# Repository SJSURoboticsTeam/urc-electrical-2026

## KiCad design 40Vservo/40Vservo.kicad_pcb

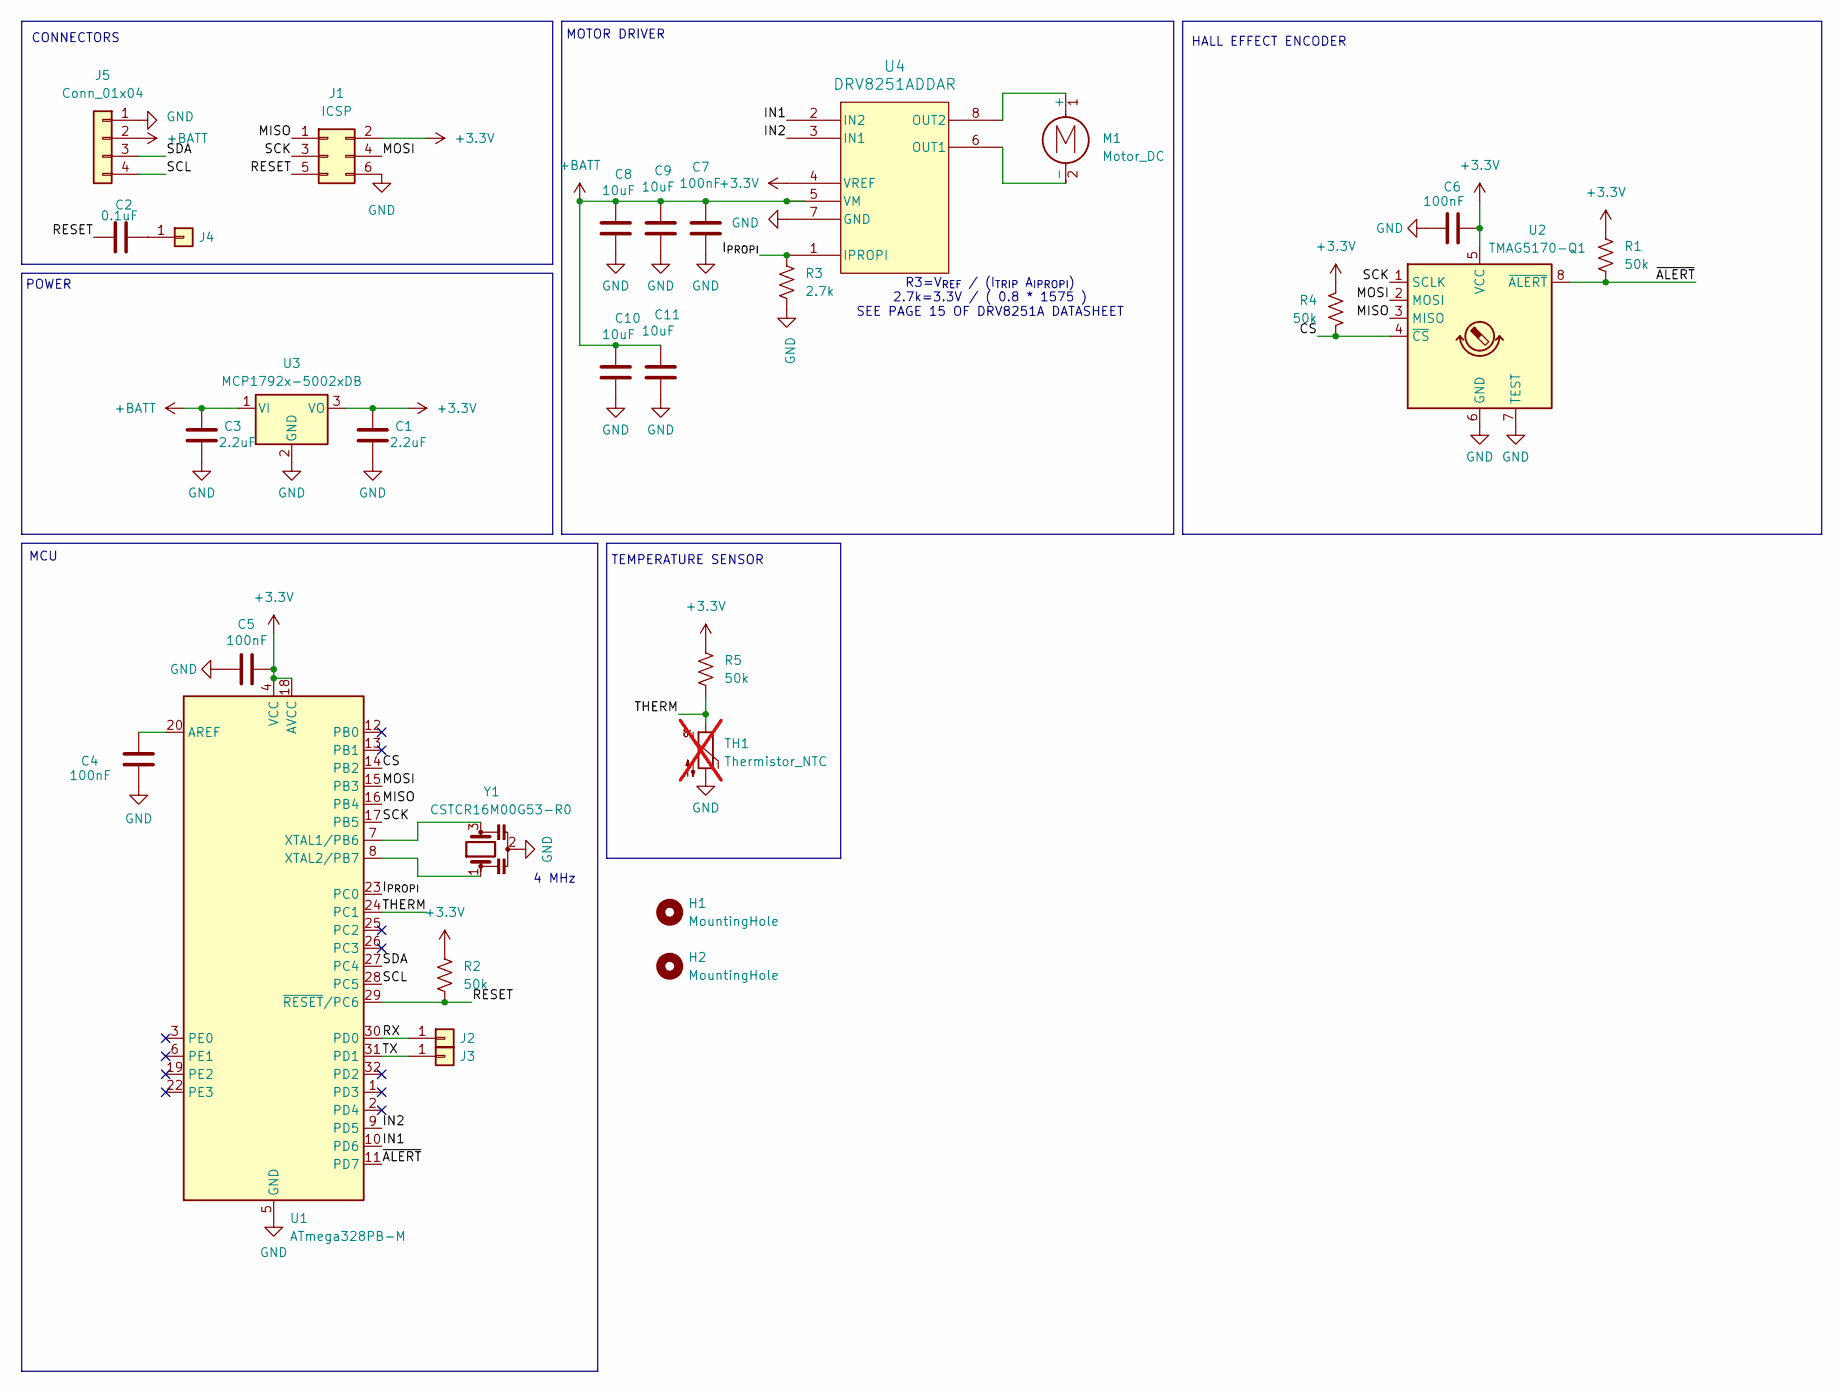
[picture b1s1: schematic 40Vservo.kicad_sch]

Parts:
C1, C3: 2.2uF; C_0603_1608Metric_Pad1.08x0.95mm_HandSolder; LCSC Part # C23630
C2: 0.1uF; C_0603_1608Metric_Pad1.08x0.95mm_HandSolder; LCSC Part # C14663
C4, C5, C6: 100nF; C_0603_1608Metric_Pad1.08x0.95mm_HandSolder; LCSC Part # C23630
C7: 100nF; C_0603_1608Metric_Pad1.08x0.95mm_HandSolder; LCSC Part # C14663
C8, C9, C10, C11: 10uF; C_0805_2012Metric_Pad1.18x1.45mm_HandSolder; LCSC Part # C440198
H1, H2: MountingHole; MountingHole_2.2mm_M2
J1: ICSP; POGO_ISP
J2, J3, J4: Conn_01x01; SolderWirePad_1x01_SMD_1x2mm
J5: Conn_01x04; SolderWire-0.5sqmm_1x04_P4.6mm_D0.9mm_OD2.1mm
M1: Motor_DC; PinHeader_1x02_P2.54mm_Vertical
R1, R2, R4, R5: 50k; R_0603_1608Metric_Pad0.98x0.95mm_HandSolder; LCSC Part # C23206
R3: 2.7k; R_0603_1608Metric_Pad0.98x0.95mm_HandSolder; LCSC Part # C13167
TH1: Thermistor_NTC; R_0603_1608Metric_Pad0.98x0.95mm_HandSolder; not fitted
U1: ATmega328PB-M; QFN-32-1EP_5x5mm_P0.5mm_EP3.1x3.1mm; LCSC Part # C967933
U2: TMAG5170-Q1; VSSOP-8_3.0x3.0mm_P0.65mm
U3: MCP1792x-5002xDB; SOT-223-3_TabPin2
U4: DRV8251ADDAR; Texas_HSOP-8-1EP_3.9x4.9mm_P1.27mm; LCSC Part # C5218844
Y1: CSTCR16M00G53-R0; Resonator_SMD_Murata_CSTxExxV-3Pin_3.0x1.1mm_HandSoldering

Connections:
+3.3V: C1.1, C5.2, C6.2, J1.2, R1.1, R2.1, R4.2, R5.1, U1.4 (VCC), U1.18 (AVCC), U2.5 (VCC), U3.3 (VO), U4.4 (VREF)
+BATT: C2.2, C3.1, C7.1, C8.1, C9.1, C10.1, C11.1, J4.1, J5.2, U3.1 (VI), U4.5 (VM)
/CS: R4.1, U1.14 (PB2), U2.4 (~CS)
/IN1: U1.10 (PD6), U4.2 (IN2)
/IN2: U1.9 (PD5), U4.3 (IN1)
/I_{PROPI}: R3.1, U1.23 (PC0), U4.1 (IPROPI)
/MISO: J1.1, U1.16 (PB4), U2.3 (MISO)
/MOSI: J1.4, U1.15 (PB3), U2.2 (MOSI)
/RX: J2.1, U1.30 (PD0)
/SCK: J1.3, U1.17 (PB5), U2.1 (SCLK)
/SCL: J5.4, U1.28 (PC5)
/SDA: J5.3, U1.27 (PC4)
/THERM: R5.2, TH1.1, U1.24 (PC1)
/TX: J3.1, U1.31 (PD1)
/~ALERT: R1.2, U1.11 (PD7), U2.8 (~ALERT)
unnamed: M1.1 (+), U4.8 (OUT2)
unnamed: M1.2 (-), U4.6 (OUT1)
unnamed: C4.2, U1.20 (AREF)
unnamed: U1.7 (XTAL1/PB6), Y1.3
unnamed: U1.8 (XTAL2/PB7), Y1.1

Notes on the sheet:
4 MHz
HALL EFFECT ENCODER
MCU
MOTOR DRIVER
TEMPERATURE SENSOR
R3=V_{REF} / (I_{TRIP} A_{IPROPI}) 2.7k=3.3V / ( 0.8 * 1575 ) SEE PAGE 15 OF DRV8251A DATASHEET
POWER
CONNECTORS

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
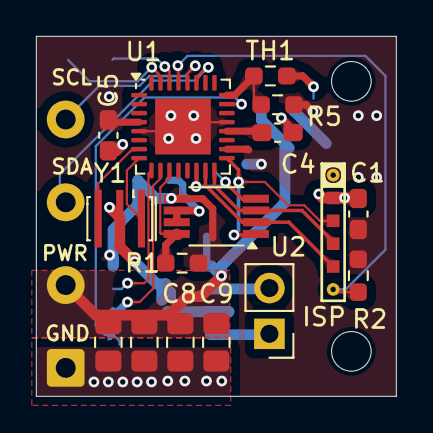
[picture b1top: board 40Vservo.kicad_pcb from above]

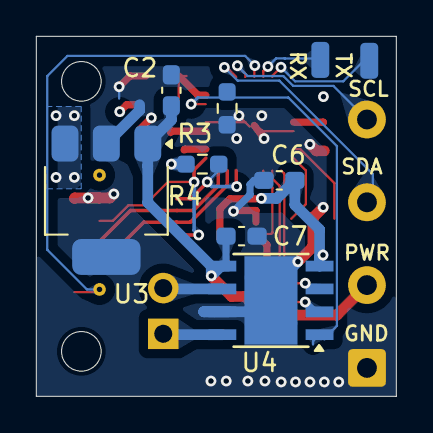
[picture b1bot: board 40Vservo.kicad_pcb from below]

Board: 4 copper layers, 20.0 x 20.0 mm, 28 parts (10 on the bottom side), 22 nets.

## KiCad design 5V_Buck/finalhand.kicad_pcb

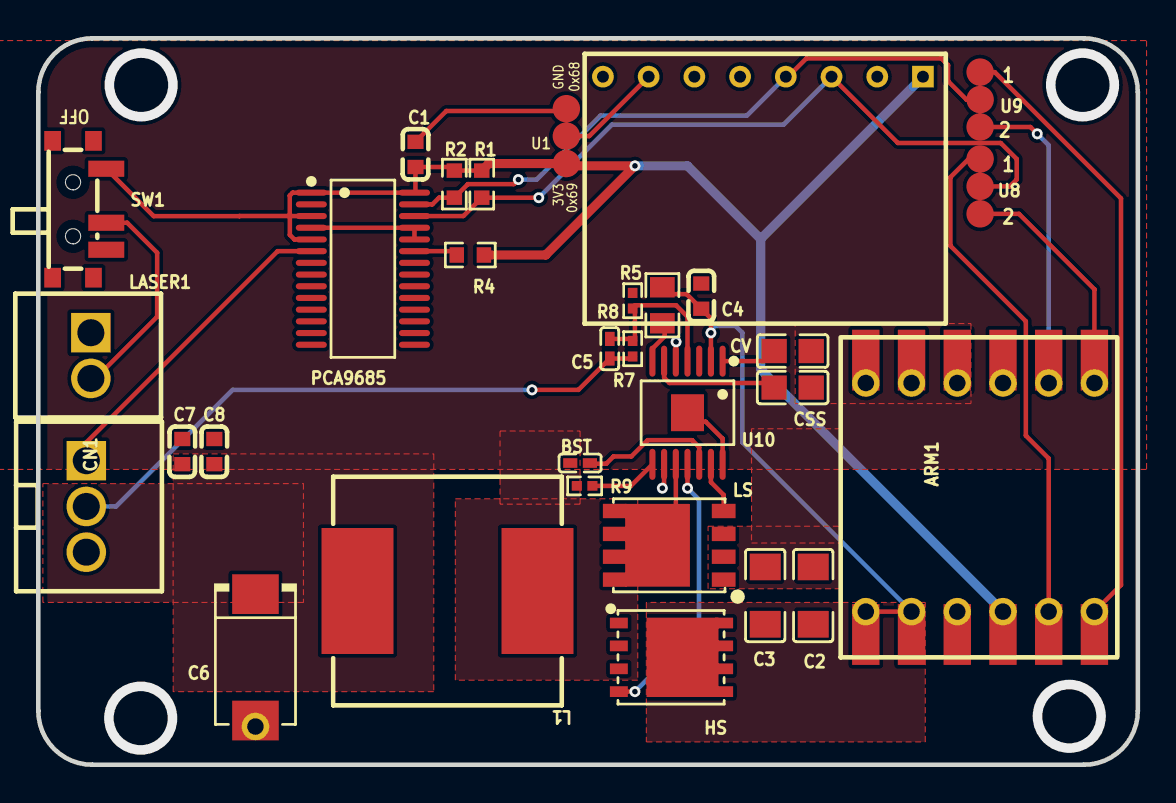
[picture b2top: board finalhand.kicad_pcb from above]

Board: 4 copper layers, 61.1 x 40.4 mm, 31 parts (0 on the bottom side), 23 nets.

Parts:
ARM1: USB-C Stubby
BST: C0402
C1, C4, C7, C8: C0603
C2, C3: C1206
C5: C0402
C6: CAP-SMD_L7.3-W4.3-R-RD
CN1: CONN-TH_3P-P2.54_KF2EDGV-2.54-3P
CSS: C0805
CV: C0805
HS: DFN-8_L5.9-W5.2-P1.27-LS6.2-BL
L1: IND-SMD_L12.7-W12.7
LASER1: CONN-TH_KF2EDGV-2.54-2P
LS: POWERVDFN-8_L6.0-W5.0-P1.27-BL
PCA9685: TSSOP-28_L9.7-W4.4-P0.65-LS6.4-BL
R1, R2, R4: R0603
R5: R0805
R7, R8, R9: R0402
SW1: SW-SMD_MK-12C02-G020
U1: MPU6050 AD0 Breakout
U6: MPU-6050 MODULE
U8, U9: 3 Pad Jumper
U10: HTSSOP-14_L5.0-W4.4-P0.65-LS6.4-BL-EP

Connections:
3V3: ARM1.4, C1.2, PCA9685.1, PCA9685.3, PCA9685.5, PCA9685.28, R1.2, R2.2, R4.2, SW1.1, U1.3, U6.1
5V: C5.1, C6.1, C7.1, C8.1, CN1.2, L1.2, R7.2
$1N15372: LASER1.2, SW1.2
$1N15383: PCA9685.23, R4.1
$2N671: BST.1, U10.12
$2N681: R5.1, U10.7
$2N1026: CSS.2, U10.6
$2N1121: CV.2, U10.1
$2N1983: C5.2, R7.1, R8.2, U10.4
$2N2778: BST.2, HS.1, HS.2, HS.3, L1.1, LS.5, LS.6, LS.7, LS.8, LS.9, R9.2, U10.10
$2N2800: LS.4, U10.13
$2N2931: R9.1, U10.8
AD0: U1.2, U6.7
GATE: HS.4, U10.11
GND: ARM1.10, ARM1.11, ARM1.12, C1.1, C2.1, C3.1, C4.1, C6.2, C7.2, C8.2, CN1.3, CSS.1, CV.1, LASER1.1, LS.1, LS.2, LS.3, PCA9685.2, PCA9685.4, PCA9685.14, PCA9685.24, PCA9685.25, R8.1, SW1.6, SW1.7, U1.1, U6.2, U10.5, U10.9, U10.14, U10.15
I2C_SCL: ARM1.7, U8.1
I2C_SCL1: ARM1.5, U8.3
I2C_SDA: ARM1.8, U9.1
I2C_SDA1: ARM1.6, U9.3
SCL: PCA9685.26, R1.1, U6.3, U8.2
SDA: PCA9685.27, R2.1, U6.4, U9.2
SERVO: CN1.1, PCA9685.6
VARM: ARM1.1, ARM1.2, C2.2, C3.2, C4.2, HS.5, HS.6, HS.7, HS.8, HS.9, R5.2, U10.2

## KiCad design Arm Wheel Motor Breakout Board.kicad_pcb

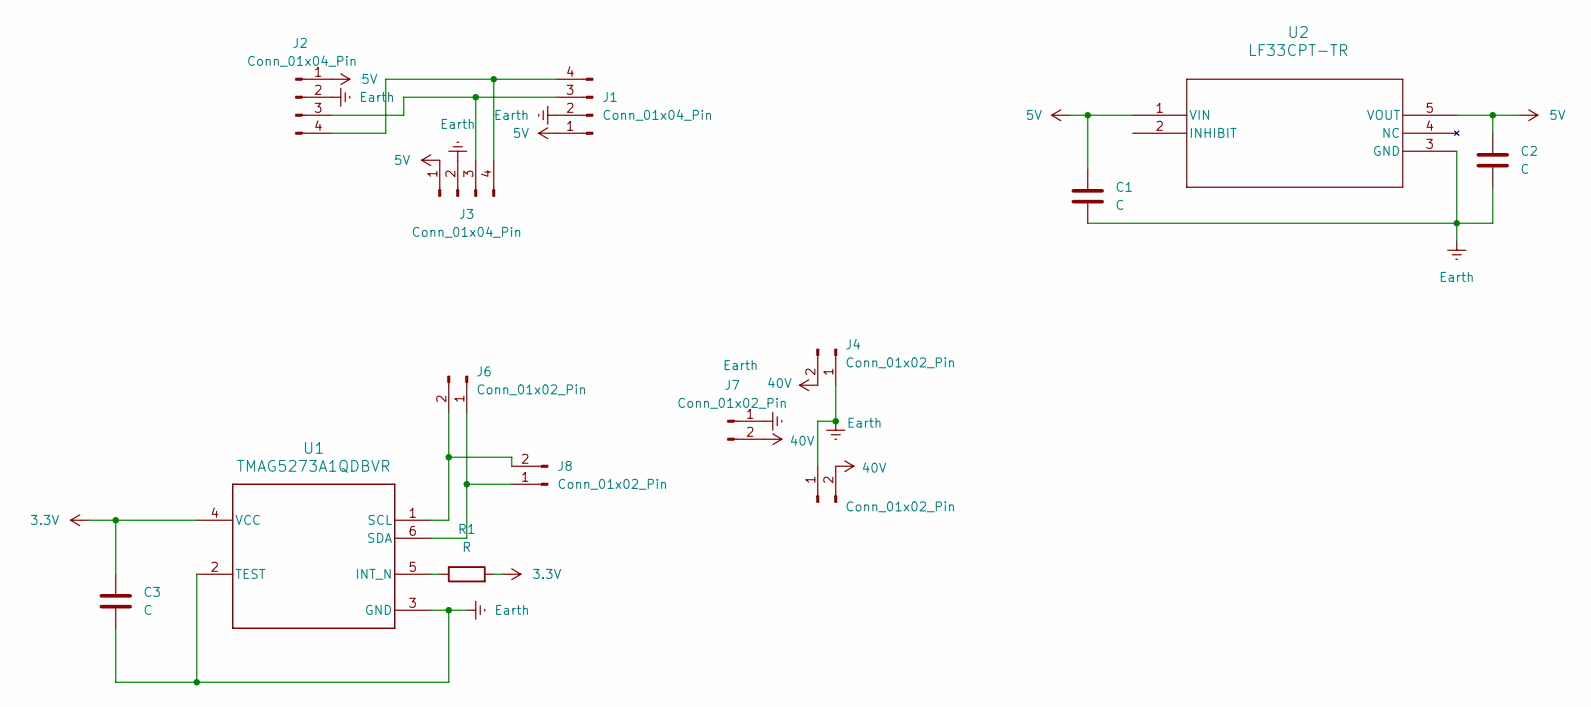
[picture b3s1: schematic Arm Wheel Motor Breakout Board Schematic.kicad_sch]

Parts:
C1, C2, C3: C; C_0201_0603Metric
J1, J2, J3: Conn_01x04_Pin; PhoenixContact_MC_1,5_4-G-3.5_1x04_P3.50mm_Horizontal
J4, J5, J7: Conn_01x02_Pin; AMASS_XT60PW-M_1x02_P7.20mm_Horizontal
J6, J8: Conn_01x02_Pin; PhoenixContact_MC_1,5_2-G-3.5_1x02_P3.50mm_Horizontal
R1: R; R_0201_0603Metric
U1: TMAG5273A1QDBVR; DBV0006A-IPC_A
U2: LF33CPT-TR; PPAK_CPT-TR_STM

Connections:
3.3V: C3.1, R1.2, U1.4 (VCC)
5V: C1.1, C2.1, J1.1, J2.1, J3.1, U2.1 (VIN), U2.5 (VOUT)
40V: J4.2, J5.2, J7.2
Earth: C1.2, C2.2, C3.2, J1.2, J2.2, J3.2, J4.1, J5.1, J7.1, U1.2 (TEST), U1.3 (GND), U2.3 (GND)
unnamed: J1.3, J2.3, J3.3
unnamed: J1.4, J2.4, J3.4
unnamed: J6.1, J8.1, U1.6 (SDA)
unnamed: J6.2, J8.2, U1.1 (SCL)
unnamed: R1.1, U1.5 (INT_N)

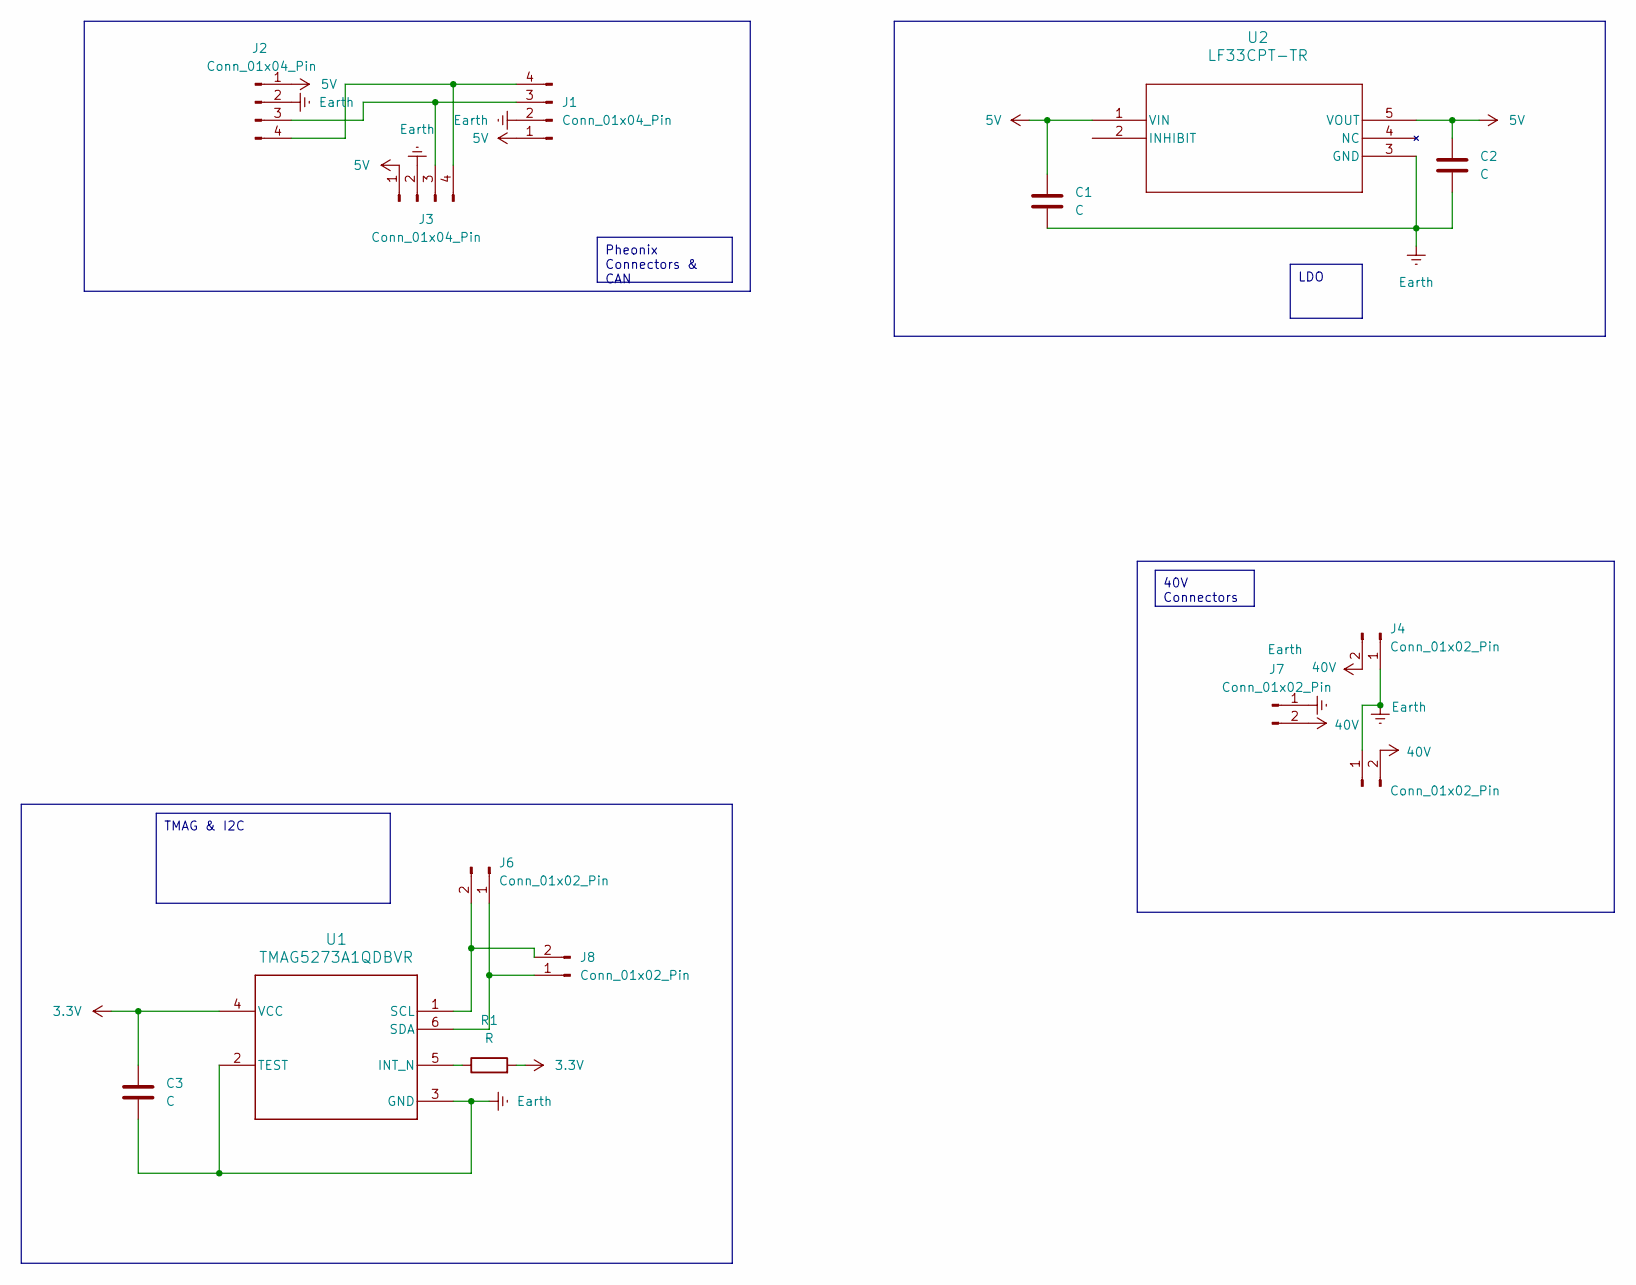
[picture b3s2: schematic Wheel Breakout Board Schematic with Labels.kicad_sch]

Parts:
C1, C2, C3: C; C_0201_0603Metric
J1, J2, J3: Conn_01x04_Pin; PhoenixContact_MC_1,5_4-G-3.5_1x04_P3.50mm_Horizontal
J4, J5, J7: Conn_01x02_Pin; AMASS_XT60PW-M_1x02_P7.20mm_Horizontal
J6, J8: Conn_01x02_Pin; PhoenixContact_MC_1,5_2-G-3.5_1x02_P3.50mm_Horizontal
R1: R; R_0201_0603Metric
U1: TMAG5273A1QDBVR; DBV0006A-IPC_A
U2: LF33CPT-TR; PPAK_CPT-TR_STM

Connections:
3.3V: C3.1, R1.2, U1.4 (VCC)
5V: C1.1, C2.1, J1.1, J2.1, J3.1, U2.1 (VIN), U2.5 (VOUT)
40V: J4.2, J5.2, J7.2
Earth: C1.2, C2.2, C3.2, J1.2, J2.2, J3.2, J4.1, J5.1, J7.1, U1.2 (TEST), U1.3 (GND), U2.3 (GND)
unnamed: J1.3, J2.3, J3.3
unnamed: J1.4, J2.4, J3.4
unnamed: J6.1, J8.1, U1.6 (SDA)
unnamed: J6.2, J8.2, U1.1 (SCL)
unnamed: R1.1, U1.5 (INT_N)

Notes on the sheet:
LDO
TMAG & I2C
Pheonix Connectors & CAN
40V Connectors

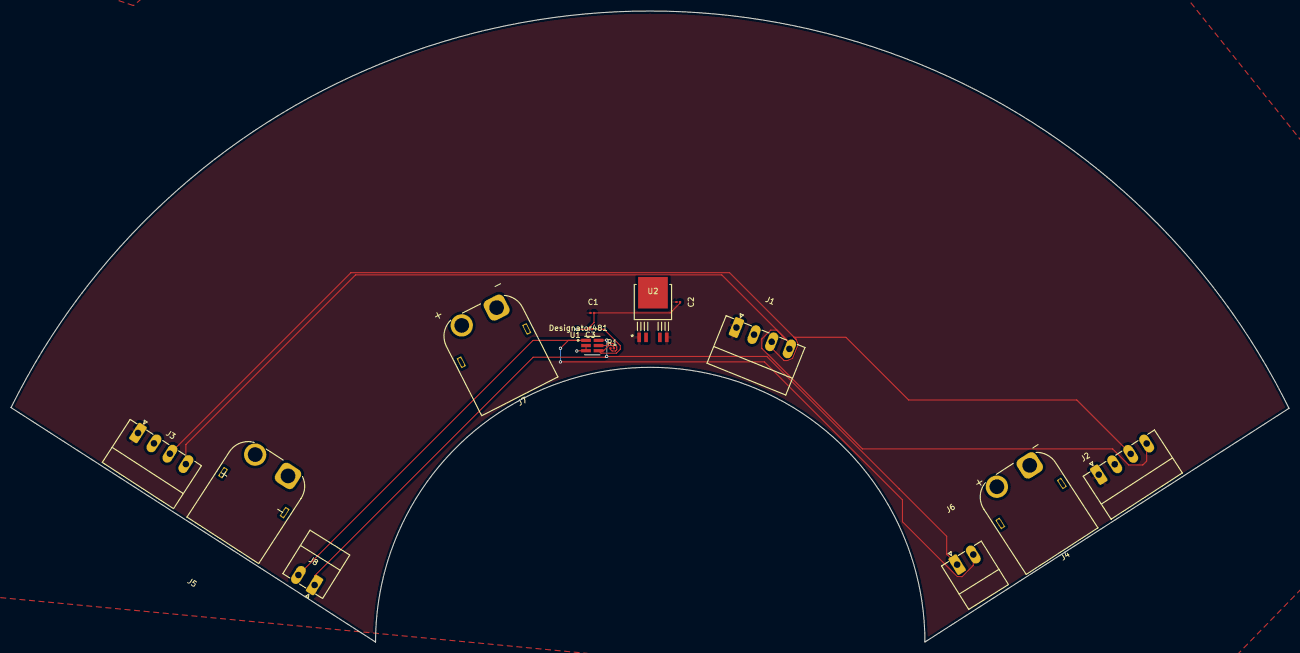
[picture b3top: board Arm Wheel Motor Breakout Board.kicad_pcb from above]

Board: 4 copper layers, 234.9 x 116.0 mm, 14 parts (0 on the bottom side), 9 nets.

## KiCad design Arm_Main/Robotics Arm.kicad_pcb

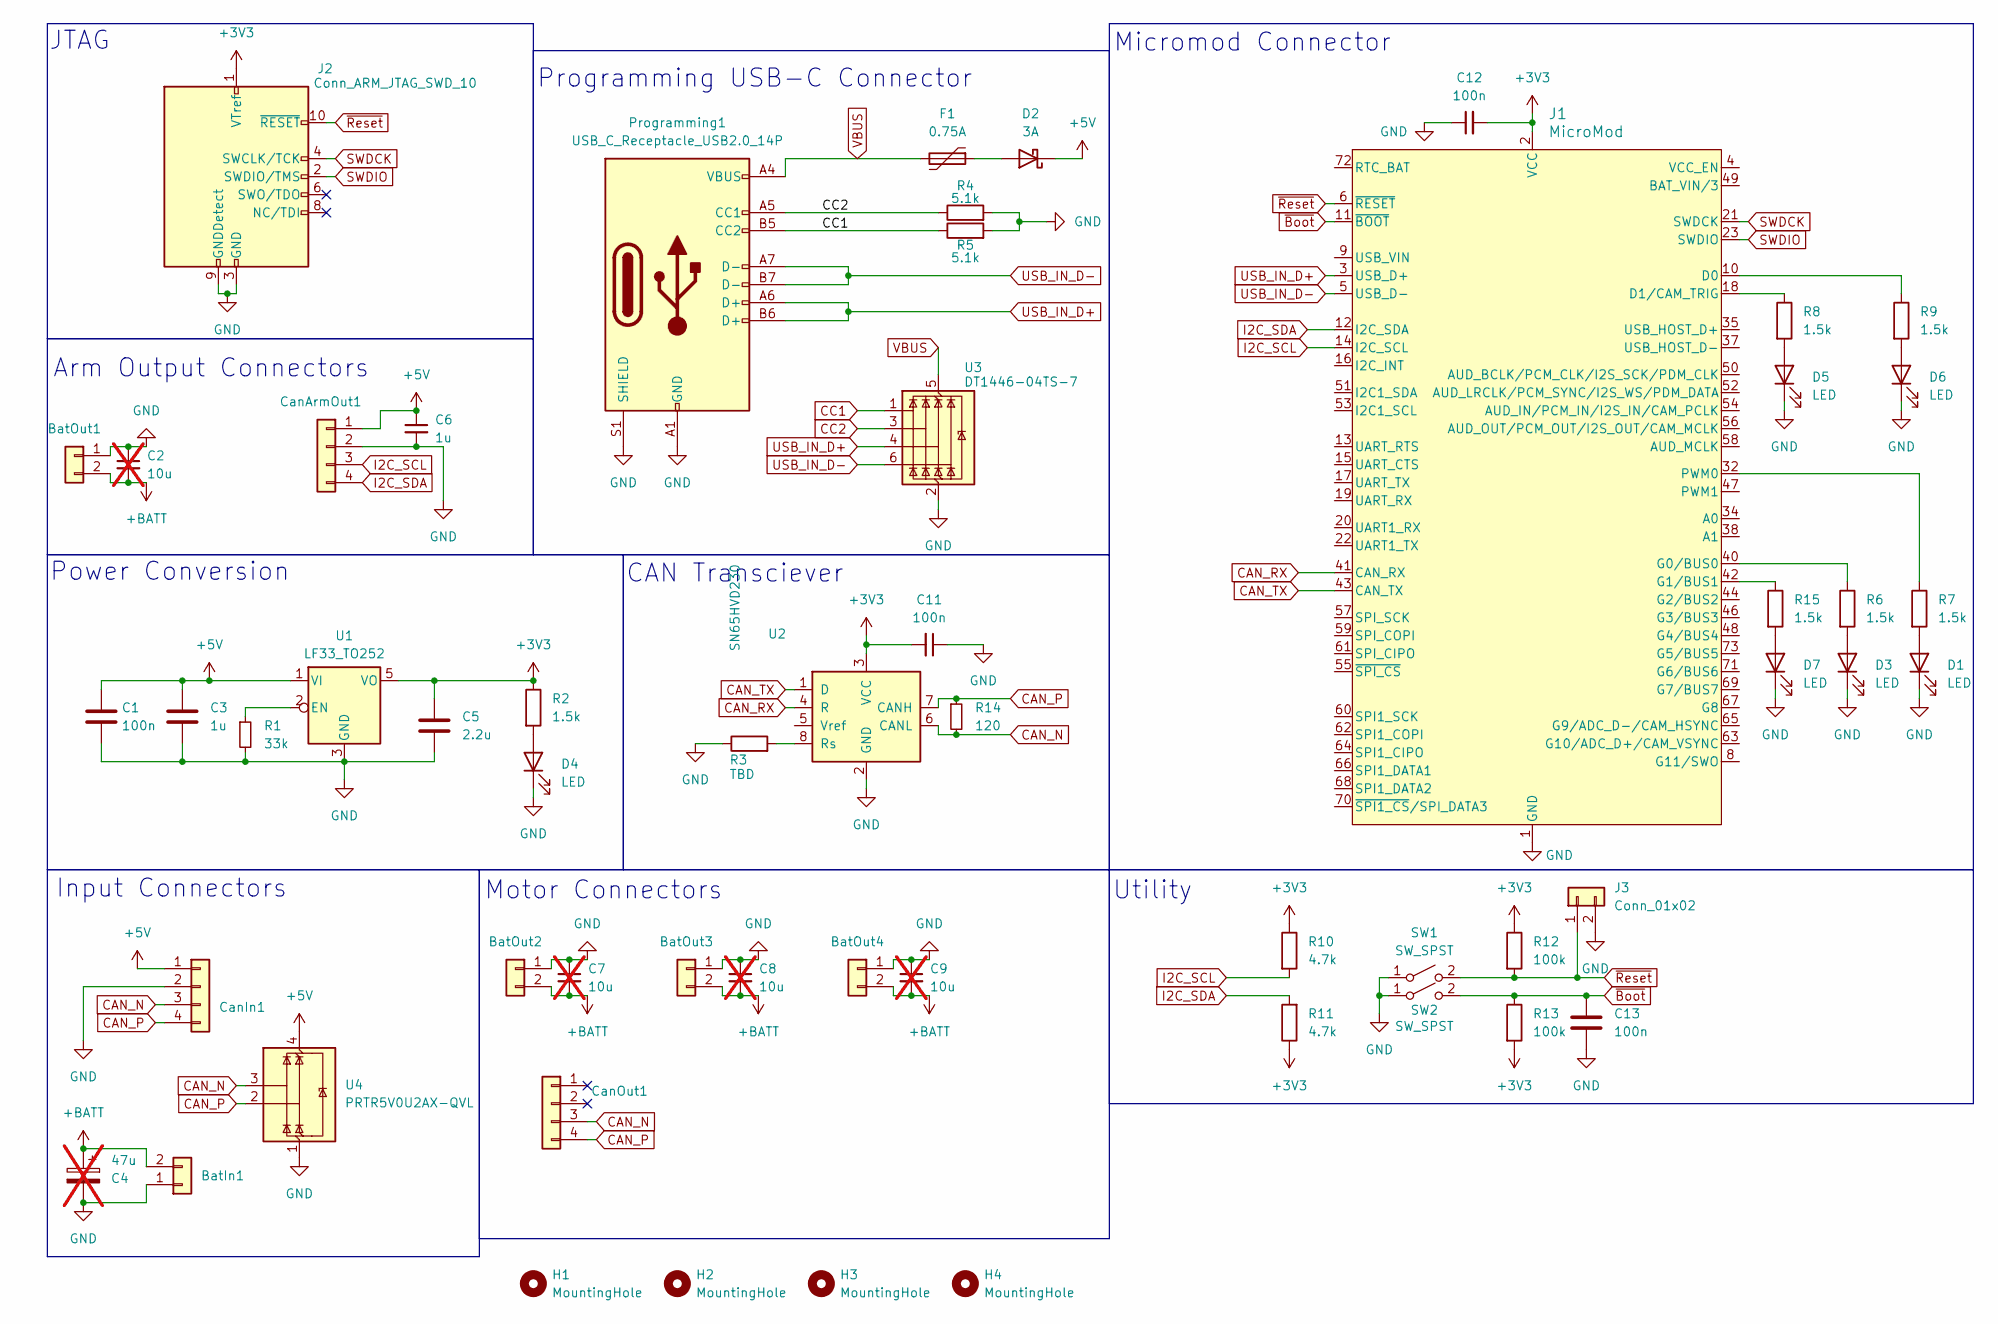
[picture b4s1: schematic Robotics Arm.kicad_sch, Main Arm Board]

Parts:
BatIn1: Conn_01x02_MountingPin; AMASS_XT60PW-F_1x02_P7.20mm_Horizontal
BatOut1, BatOut2, BatOut3, BatOut4: Conn_01x02_MountingPin; AMASS_XT60PW-F_1x02_P7.20mm_Horizontal
C1, C11, C12, C13: 100n; C_0603_1608Metric_Pad1.08x0.95mm_HandSolder
C2, C7, C8, C9: 10u; C_0603_1608Metric_Pad1.08x0.95mm_HandSolder; not fitted
C3, C6: 1u; C_0603_1608Metric_Pad1.08x0.95mm_HandSolder
C4: 47u; CP_Radial_D6.3mm_P2.50mm; not fitted
C5: 2.2u; C_0603_1608Metric_Pad1.08x0.95mm_HandSolder
CanArmOut1: Conn_01x04_MountingPin; Pluggable_Terminal_2.54mm_4P_Horizontal
CanIn1: Conn_01x04_MountingPin; Pluggable_Terminal_2.54mm_4P_Horizontal
CanOut1: Conn_01x04_MountingPin; Pluggable_Terminal_2.54mm_4P_Vertical
D1, D3, D4, D5, D6, D7: LED; LED_0603_1608Metric_Pad1.05x0.95mm_HandSolder
D2: 3A; DO-221AC
F1: 0.75A; Fuse_1206_3216Metric_Pad1.42x1.75mm_HandSolder; Part Number SMD1206B075TFT
H1, H2, H3, H4: MountingHole; MountingHole_3.2mm_M3
J1: MicroMod; micromod
J2: Conn_ARM_JTAG_SWD_10; PinHeader_2x05_P1.27mm_Vertical
J3: Conn_01x02; PinHeader_1x02_P2.54mm_Vertical
Programming1: USB_C_Receptacle_USB2.0_14P; USB_C_Receptacle_HRO_TYPE-C-31-M-12
R1: 33k; R_0603_1608Metric_Pad0.98x0.95mm_HandSolder
R2, R6, R7, R8, R9, R15: 1.5k; R_0603_1608Metric_Pad0.98x0.95mm_HandSolder
R3: TBD; R_0603_1608Metric_Pad0.98x0.95mm_HandSolder
R4, R5: 5.1k; R_0603_1608Metric_Pad0.98x0.95mm_HandSolder
R10, R11: 4.7k; R_0603_1608Metric_Pad0.98x0.95mm_HandSolder
R12, R13: 100k; R_0603_1608Metric_Pad0.98x0.95mm_HandSolder
R14: 120; R_0603_1608Metric_Pad0.98x0.95mm_HandSolder
SW1, SW2: SW_SPST; SW_SPST_CK_RS282G05A3
U1: LF33_TO252; TO-252AD
U2: SN65HVD230; SOIC-8_3.9x4.9mm_P1.27mm
U3: DT1446-04TS-7; SOT-23-6
U4: PRTR5V0U2AX-QVL; SOT-143_Handsoldering

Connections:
+3V3: C5.1, C11.2, C12.2, J1.2 (VCC), J1.74 (VCC), J2.1 (VTref), R2.1, R10.1, R11.1, R12.1, R13.2, U1.5 (VO), U2.3 (VCC)
+5V: C1.1, C3.1, C6.1, CanArmOut1.1, CanIn1.1, D2.1 (K), U1.1 (VI), U4.4 (VBUS)
+BATT: BatIn1.2, BatOut1.2, BatOut2.2, BatOut3.2, BatOut4.2, C2.2, C4.1, C7.2, C8.2, C9.2
CAN_N: CanIn1.3, CanOut1.3, R14.2, U2.6 (CANL), U4.3 (I/O2)
CAN_P: CanIn1.4, CanOut1.4, R14.1, U2.7 (CANH), U4.2 (I/O3)
CAN_RX: J1.41 (CAN_RX), U2.4 (R)
CAN_TX: J1.43 (CAN_TX), U2.1 (D)
CC1: Programming1.B5 (CC2), R5.1, U3.1 (I/O1)
CC2: Programming1.A5 (CC1), R4.1, U3.3 (I/O2)
GND: BatIn1.1, BatOut1.1, BatOut2.1, BatOut3.1, BatOut4.1, C1.2, C2.1, C3.2, C4.2, C5.2, C6.2, C7.1, C8.1, C9.1, C11.1, C12.1, C13.2, CanArmOut1.2, CanIn1.2, D1.1 (K), D3.1 (K), D4.1 (K), D5.1 (K), D6.1 (K), D7.1 (K), J1.1 (GND), J1.7 (GND), J1.33 (GND), J1.36 (GND), J1.39 (GND), J1.45 (GND), J1.75 (GND), J1.S1 (GND), J1.S2 (GND), J1.S3 (GND), J2.3 (GND), J2.5 (GND), J2.9 (GNDDetect), J3.2, Programming1.A1 (GND), Programming1.A12 (GND), Programming1.B1 (GND), Programming1.B12 (GND), Programming1.S1 (SHIELD), R1.2, R3.1, R4.2, R5.2, SW1.1 (A), SW2.1 (A), U1.3 (GND), U2.2 (GND), U3.2 (GND), U4.1 (GND)
I2C_SCL: CanArmOut1.3, J1.14 (I2C_SCL), R10.2
I2C_SDA: CanArmOut1.4, J1.12 (I2C_SDA), R11.2
unnamed: D1.2 (A), R7.2
unnamed: D2.2 (A), F1.1
unnamed: D3.2 (A), R6.2
unnamed: D4.2 (A), R2.2
unnamed: D5.2 (A), R8.2
unnamed: D6.2 (A), R9.2
unnamed: D7.2 (A), R15.2
unnamed: J1.10 (D0), R9.1
unnamed: J1.18 (D1/CAM_TRIG), R8.1
unnamed: J1.40 (G0/BUS0), R6.1
unnamed: J1.42 (G1/BUS1), R15.1
unnamed: J1.32 (PWM0), R7.1
unnamed: R1.1, U1.2 (EN)
unnamed: R3.2, U2.8 (Rs)
SWDCK: J1.21 (SWDCK), J2.4 (SWCLK/TCK)
SWDIO: J1.23 (SWDIO), J2.2 (SWDIO/TMS)
USB_IN_D+: J1.3 (USB_D+), Programming1.A6 (D+), Programming1.B6 (D+), U3.4 (I/O3)
USB_IN_D-: J1.5 (USB_D-), Programming1.A7 (D-), Programming1.B7 (D-), U3.6 (I/O4)
VBUS: F1.2, Programming1.A4 (VBUS), Programming1.A9 (VBUS), Programming1.B4 (VBUS), Programming1.B9 (VBUS), U3.5 (VBUS)
~Boot: C13.1, J1.11 (~BOOT), R13.1, SW2.2 (B)
~Reset: J1.6 (~RESET), J2.10 (~RESET), J3.1, R12.2, SW1.2 (B)

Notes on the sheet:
Arm Output Connectors
Micromod Connector
Utility
Input Connectors
CAN Transciever
Motor Connectors
Power Conversion
Programming USB-C Connector
JTAG

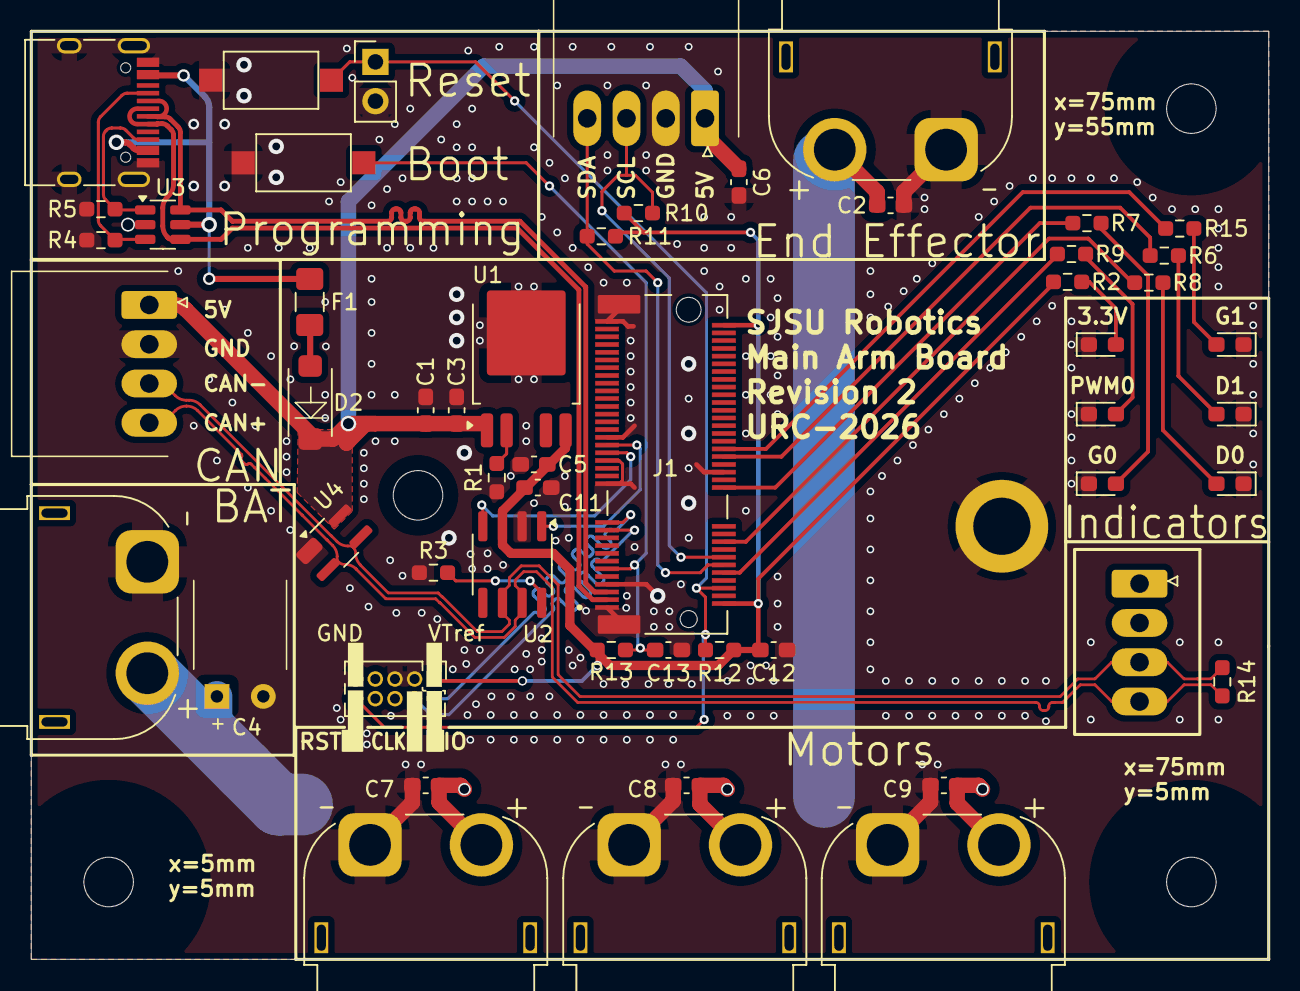
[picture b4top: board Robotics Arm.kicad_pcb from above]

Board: 2 copper layers, 80.0 x 60.0 mm, 57 parts (0 on the bottom side), 33 nets.

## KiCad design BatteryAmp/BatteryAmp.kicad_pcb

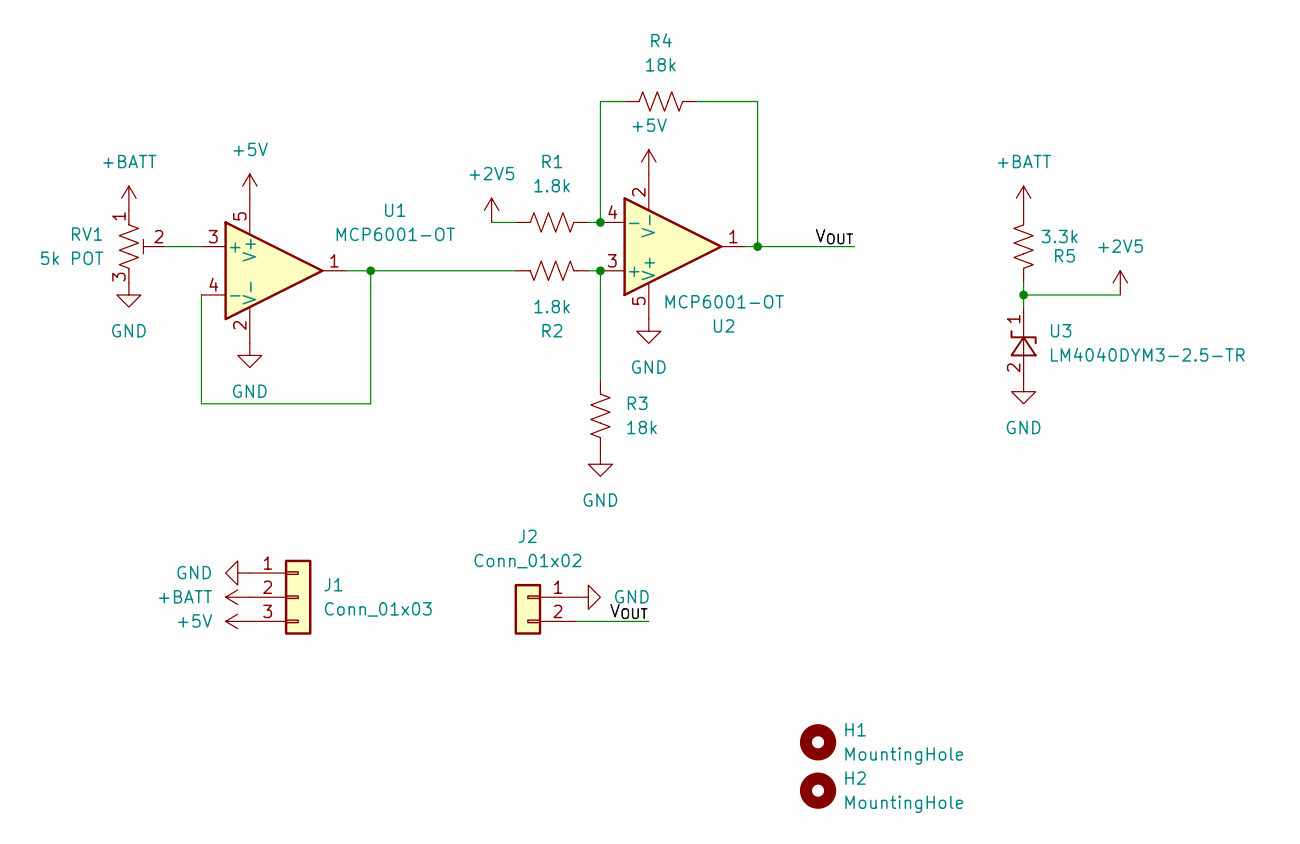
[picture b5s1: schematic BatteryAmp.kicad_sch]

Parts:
H1, H2: MountingHole; MountingHole_3.2mm_M3
J1: Conn_01x03; PinSocket_1x03_P2.54mm_Vertical
J2: Conn_01x02; PinHeader_1x02_P2.54mm_Vertical
R1, R2: 1.8k; R_0603_1608Metric
R3, R4: 18k; R_0603_1608Metric
R5: 3.3k; R_0603_1608Metric
RV1: 5k POT; Potentiometer_Bourns_3361P_Vertical
U1, U2: MCP6001-OT; SOT-23-5
U3: LM4040DYM3-2.5-TR; SOT-23

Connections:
+2V5: R1.1, R5.1, U3.1 (K)
+5V: J1.3, U1.5 (V+), U2.2 (V-)
+BATT: J1.2, R5.2, RV1.1
/V_{OUT}: J2.2, R4.2, U2.1
GND: J1.1, J2.1, R3.1, RV1.3, U1.2 (V-), U2.5 (V+), U3.2 (A)
unnamed: RV1.2, U1.3 (+)
unnamed: R2.1, U1.1, U1.4 (-)
unnamed: R2.2, R3.2, U2.3 (+)
unnamed: R1.2, R4.1, U2.4 (-)

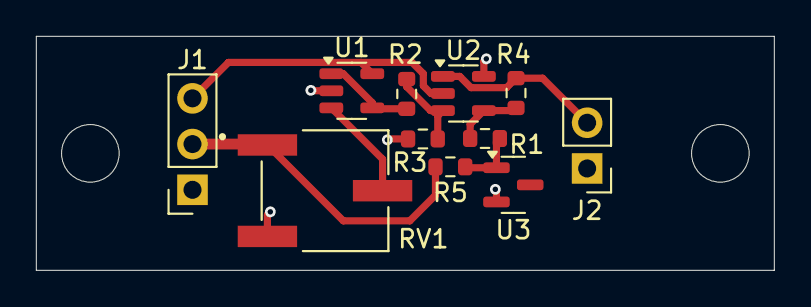
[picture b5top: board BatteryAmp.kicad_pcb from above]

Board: 2 copper layers, 41.0 x 13.0 mm, 13 parts (0 on the bottom side), 9 nets.

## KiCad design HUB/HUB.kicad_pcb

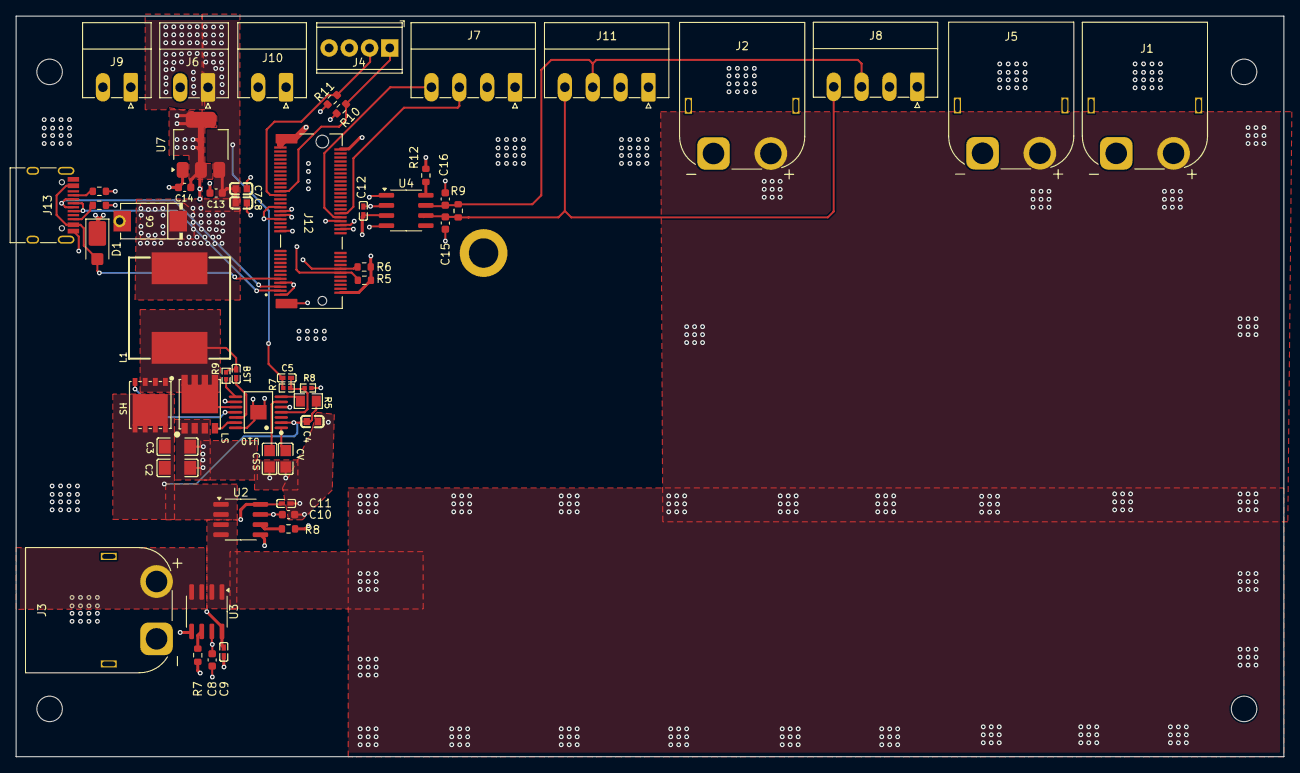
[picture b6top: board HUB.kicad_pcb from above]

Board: 4 copper layers, 159.2 x 93.0 mm, 55 parts (0 on the bottom side), 35 nets.

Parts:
BST: C0402
C2, C3: C1206
C4, C7, C8#2: C0603
C5: C0402
C6: CAP-SMD_L7.3-W4.3-R-RD
C8, C10: 18pF; C_0603_1608Metric
C9, C11, C12: 100nF; C0402
C13, C14: 10µF; C_0603_1608Metric
C15, C16: 18pf; C_0603_1608Metric
CSS: C0805
CV: C0805
D1: D; Vishay_SMPA
HS: DFN-8_L5.9-W5.2-P1.27-LS6.2-BL
J1, J2, J3, J5: XT60-PW-M; AMASS_XT60PW-M_1x02_P7.20mm_Horizontal
J4: Phoenix [2.54mm]; TerminalBlock_Phoenix_MPT-0,5-4-2.54_1x04_P2.54mm_Horizontal
J6, J10: Phoenix (5V,GND); PhoenixContact_MC_1,5_2-G-3.5_1x02_P3.50mm_Horizontal
J7: Phoenix (GPIO, 5V, GND); PhoenixContact_MC_1,5_4-G-3.5_1x04_P3.50mm_Horizontal
J8, J11: Phoenix (+,-,CANH/L); PhoenixContact_MC_1,5_4-G-3.5_1x04_P3.50mm_Horizontal
J9: Phoenix (SDA/L); PhoenixContact_MC_1,5_2-G-3.5_1x02_P3.50mm_Horizontal
J12: MicroMod; micromod
J13: USB_C_Receptacle_USB2.0_14P; USB_C_Receptacle_HRO_TYPE-C-31-M-12
L1: IND-SMD_L12.7-W12.7
LS: POWERVDFN-8_L6.0-W5.0-P1.27-BL
R5, R6, R7, R8, R10, R11: 10K; R_0603_1608Metric
R5#2: R0805
R7#2, R8#2, R9: R0402
R9#2, R12: 120; R_0603_1608Metric
R13, R14: 5.1k; R_0603_1608Metric
U2, U3: ACS711xLCTR-25AB; SOIC-8_3.9x4.9mm_P1.27mm
U4: SN65HVD230; SOIC-8_3.9x4.9mm_P1.27mm
U7: AMS1117-3.3; SOT-223-3_TabPin2
U10: HTSSOP-14_L5.0-W4.4-P0.65-LS6.4-BL-EP

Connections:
3.3V: C9.1, C11.1, C12.1, C14.1, J12.2 (VCC), J12.74 (VCC), R5.1, R6.1, R7.2, R8.2, R10.1, R11.1, U2.8 (VCC), U3.8 (VCC), U4.3 (VCC), U7.2 (VO)
5V: C5.1, C6.1, C7.1, C8#2.1, C13.1, D1.1 (K), J4.4, J6.1, J7.1, J8.1, J10.1, J11.1, L1.2, R7#2.2, U7.3 (VI)
40V: C2.2, C3.2, C4.2, HS.5, HS.6, HS.7, HS.8, HS.9, R5#2.2, U2.1 (IP+), U2.2 (IP+), U10.2
$2N671: BST.1, U10.12
$2N681: R5#2.1, U10.7
$2N1026: CSS.2, U10.6
$2N1121: CV.2, U10.1
$2N1983: C5.2, R7#2.1, R8#2.2, U10.4
$2N2778: BST.2, HS.1, HS.2, HS.3, L1.1, LS.5, LS.6, LS.7, LS.8, LS.9, R9.2, U10.10
$2N2800: LS.4, U10.13
$2N2931: R9.1, U10.8
ADC1: C8.1, J12.34 (A0), U3.7 (VIOUT)
ADC2: C10.1, J12.38 (A1), U2.7 (VIOUT)
GATE: HS.4, U10.11
GND: C2.1, C3.1, C4.1, C6.2, C7.2, C8.2, C8#2.2, C9.2, C10.2, C11.2, C12.2, C13.2, C14.2, C15.2, C16.1, CSS.1, CV.1, J1.1, J2.1, J3.1, J4.3, J5.1, J6.2, J7.2, J8.2, J10.2, J11.2, J12.1 (GND), J12.7 (GND), J12.33 (GND), J12.36 (GND), J12.39 (GND), J12.45 (GND), J12.75 (GND), J12.S1 (GND), J12.S2 (GND), J12.S3 (GND), J13.A1 (GND), J13.A12 (GND), J13.B1 (GND), J13.B12 (GND), J13.S1 (SHIELD), LS.1, LS.2, LS.3, R8#2.1, R12.1, R13.1, R14.1, U2.5 (GND), U3.5 (GND), U4.2 (GND), U7.1 (GND), U10.5, U10.9, U10.14, U10.15
unnamed: D1.2 (A), J12.9 (USB_VIN), J13.A4 (VBUS), J13.A9 (VBUS), J13.B4 (VBUS), J13.B9 (VBUS)
unnamed: J1.2, J2.2, J5.2, U2.3 (IP-), U2.4 (IP-), U3.1 (IP+), U3.2 (IP+)
unnamed: J3.2, U3.3 (IP-), U3.4 (IP-)
unnamed: C16.2, J8.3, J11.3, R9#2.2, U4.7 (CANH)
unnamed: C15.1, J8.4, J11.4, R9#2.1, U4.6 (CANL)
unnamed: J7.4, J12.40 (G0/BUS0)
unnamed: J7.3, J12.42 (G1/BUS1)
unnamed: J12.3 (USB_D+), J13.A6 (D+), J13.B6 (D+)
unnamed: J12.5 (USB_D-), J13.A7 (D-), J13.B7 (D-)
unnamed: J13.A5 (CC1), R13.2
unnamed: J13.B5 (CC2), R14.2
unnamed: R8.1, U2.6 (~FAULT)
unnamed: R7.1, U3.6 (~FAULT)
unnamed: R12.2, U4.8 (Rs)
RX: J12.41 (CAN_RX), U4.4 (R)
SCL: J9.2, J12.14 (I2C_SCL), R6.2
SCL2: J4.1, J12.53 (I2C1_SCL), R10.2
SDA: J9.1, J12.12 (I2C_SDA), R5.2
SDA2: J4.2, J12.51 (I2C1_SDA), R11.2
TX: J12.43 (CAN_TX), U4.1 (D)
